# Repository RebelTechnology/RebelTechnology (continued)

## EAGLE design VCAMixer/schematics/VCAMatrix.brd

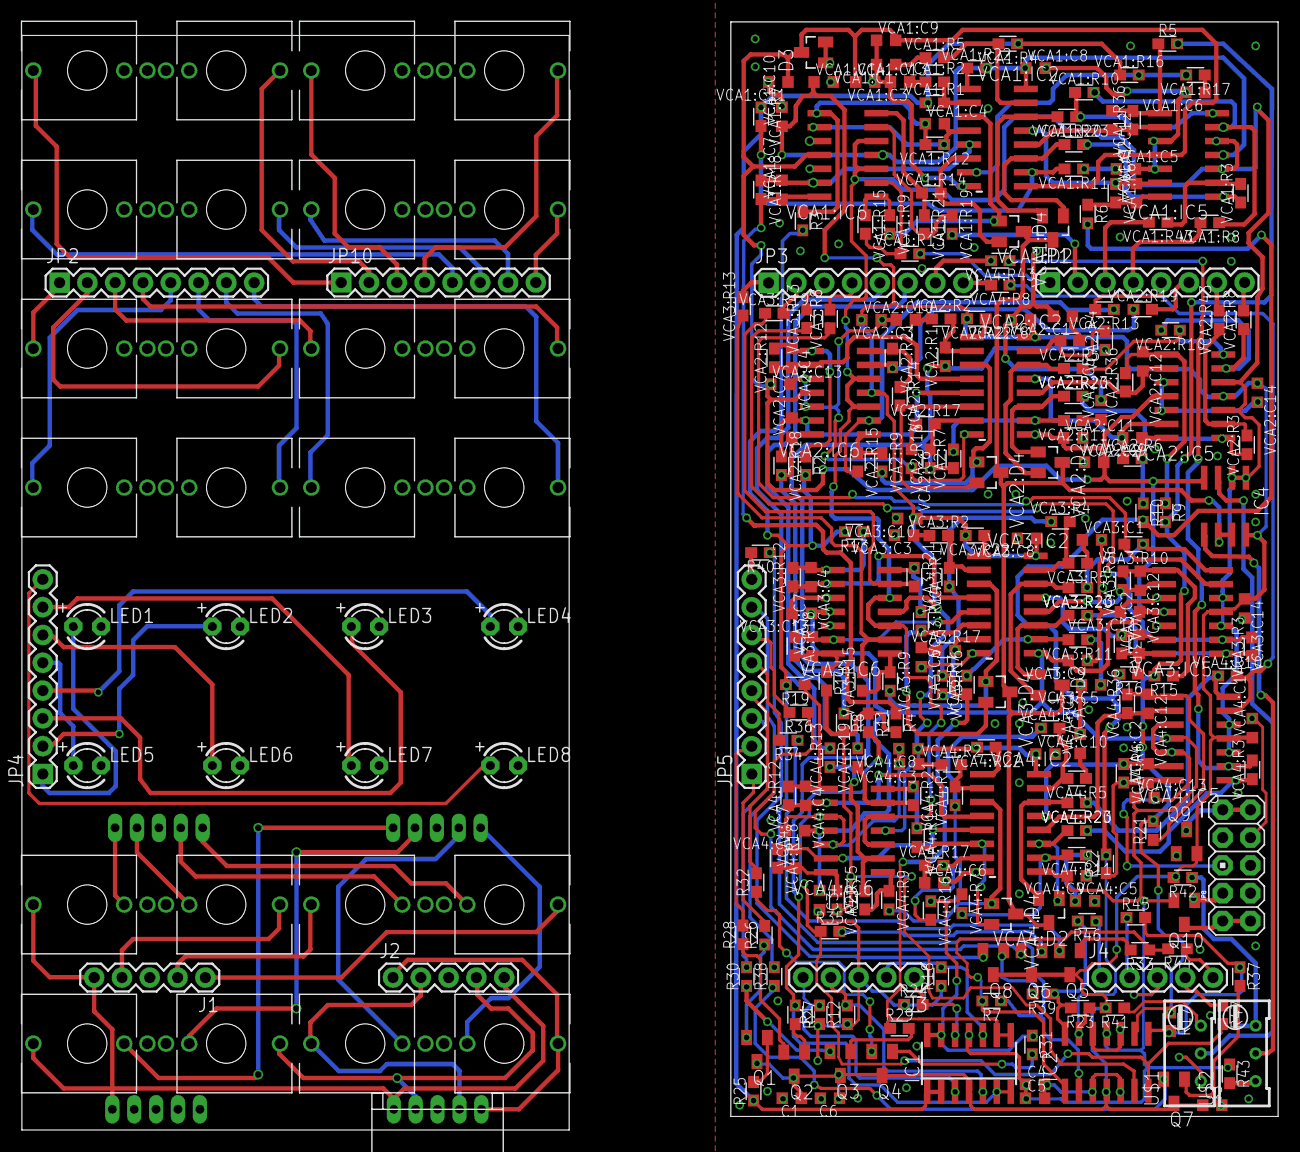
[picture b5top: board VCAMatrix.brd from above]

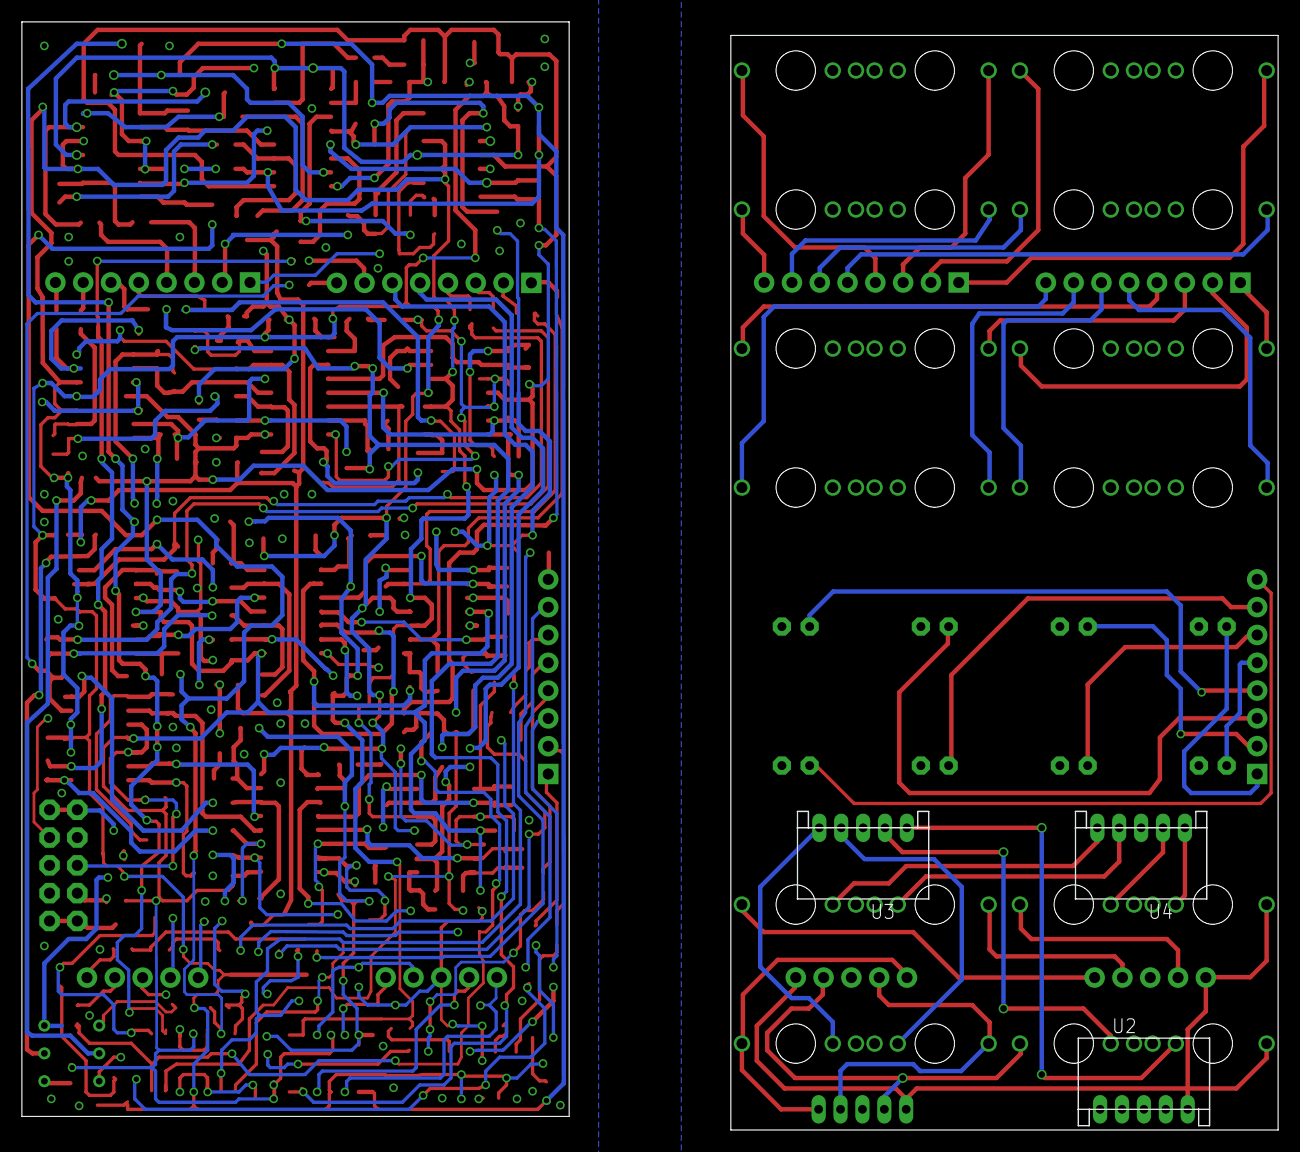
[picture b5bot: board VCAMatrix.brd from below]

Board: 2 copper layers, 50.0 x 100.0 mm, 292 parts (3 on the bottom side), 196 nets.

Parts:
C1, C2, C3, C4, C5, C6: 100n; C0603K
CV_AA: THONKICONN
CV_AB: THONKICONN
CV_AC: THONKICONN
CV_AD: THONKICONN
CV_BA: THONKICONN
CV_BB: THONKICONN
CV_BC: THONKICONN
CV_BD: THONKICONN
CV_CA: THONKICONN
CV_CB: THONKICONN
CV_CC: THONKICONN
CV_CD: THONKICONN
CV_DA: THONKICONN
CV_DB: THONKICONN
CV_DC: THONKICONN
CV_DD: THONKICONN
D3: BAT54A; SOT23
IC1: QUAD_OPAMPD; SO14
IC2: TL074D; SO14
IC4: TL072D; SO08
IN_A: THONKICONN
IN_B: THONKICONN
IN_C: THONKICONN
IN_D: THONKICONN
J1, J2, J3, J4: 1X05
JP1, JP2, JP3, JP4, JP5, JP10: 1X08
JP8: M05X2PTH; AVR_ICSP
LED1, LED2, LED3, LED4, LED5, LED6, LED7, LED8: LED3MM
OUTA: THONKICONN
OUTB: THONKICONN
OUTC: THONKICONN
OUTD: THONKICONN
Q1, Q2, Q3, Q4, Q5, Q6, Q7, Q8: BC846ALT1SMD; SOT23
Q9: BSS84; SOT23
Q10: BSS123; SOT23
R1, R2, R3, R4, R5, R6, R7, R8, R9, R10, R11, R12, R13, R14, R15, R16, R17, R18, R19, R20, R21, R22, R23, R24: 100k; 0603
R25, R27, R29, R31, R33, R35, R37, R39: 20k; 0603
R26, R28, R30, R32, R34, R36, R38, R40: 560; 0603
R41, R42, R43: 10k; 0603
R44, R45, R46, R47: 1k; 0603
U1, U2, U3, U4: CON-JST_PH_5W
U$1, U$2: RTRIM64W
VCA1:C1, VCA1:C3, VCA1:C5, VCA1:C6, VCA2:C1, VCA2:C3, VCA2:C5, VCA2:C6, VCA3:C1, VCA3:C3, VCA3:C5, VCA3:C6, VCA4:C1, VCA4:C3, VCA4:C5, VCA4:C6: 560p; C0603K
VCA1:C2, VCA1:C4, VCA1:C7, VCA1:C12, VCA2:C2, VCA2:C4, VCA2:C7, VCA2:C12, VCA3:C2, VCA3:C4, VCA3:C7, VCA3:C12, VCA4:C2, VCA4:C4, VCA4:C7, VCA4:C12: 100p; C0603K
VCA1:C8, VCA1:C9, VCA1:C10, VCA1:C11, VCA1:C13, VCA1:C14, VCA2:C8, VCA2:C9, VCA2:C10, VCA2:C11, VCA2:C13, VCA2:C14, VCA3:C8, VCA3:C9, VCA3:C10, VCA3:C11, VCA3:C13, VCA3:C14, VCA4:C8, VCA4:C9, VCA4:C10, VCA4:C11, VCA4:C13, VCA4:C14: 100n; C0603K
VCA1:D2, VCA1:D4, VCA2:D2, VCA2:D4, VCA3:D2, VCA3:D4, VCA4:D2, VCA4:D4: BAT54A; SOT23
VCA1:IC2, VCA2:IC2, VCA3:IC2, VCA4:IC2: SSM2164S; SOIC16N
VCA1:IC5, VCA1:IC6, VCA2:IC5, VCA2:IC6, VCA3:IC5, VCA3:IC6, VCA4:IC5, VCA4:IC6: TL074D; SO14
VCA1:R1, VCA1:R4, VCA1:R6, VCA1:R7, VCA1:R12, VCA1:R16, VCA1:R18, VCA1:R36, VCA2:R1, VCA2:R4, VCA2:R6, VCA2:R7, VCA2:R12, VCA2:R16, VCA2:R18, VCA2:R36, VCA3:R1, VCA3:R4, VCA3:R6, VCA3:R7, VCA3:R12, VCA3:R16, VCA3:R18, VCA3:R36, VCA4:R1, VCA4:R4, VCA4:R6, VCA4:R7, VCA4:R12, VCA4:R16, VCA4:R18, VCA4:R36: 30k; 0603
VCA1:R2, VCA1:R5, VCA1:R11, VCA1:R17, VCA2:R2, VCA2:R5, VCA2:R11, VCA2:R17, VCA3:R2, VCA3:R5, VCA3:R11, VCA3:R17, VCA4:R2, VCA4:R5, VCA4:R11, VCA4:R17: 500; 0603
VCA1:R3, VCA1:R10, VCA1:R15, VCA1:R21, VCA2:R3, VCA2:R10, VCA2:R15, VCA2:R21, VCA3:R3, VCA3:R10, VCA3:R15, VCA3:R21, VCA4:R3, VCA4:R10, VCA4:R15, VCA4:R21: 68k; 0603
VCA1:R8, VCA1:R13, VCA1:R19, VCA1:R43, VCA2:R8, VCA2:R13, VCA2:R19, VCA2:R43, VCA3:R8, VCA3:R13, VCA3:R19, VCA3:R43, VCA4:R8, VCA4:R13, VCA4:R19, VCA4:R43: 100k; 0603
VCA1:R9, VCA1:R14, VCA1:R20, VCA1:R23, VCA2:R9, VCA2:R14, VCA2:R20, VCA2:R23, VCA3:R9, VCA3:R14, VCA3:R20, VCA3:R23, VCA4:R9, VCA4:R14, VCA4:R20, VCA4:R23: 560; 0603
VCA1:R22, VCA2:R22, VCA3:R22, VCA4:R22: 6k; 0603

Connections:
+12V: C1.1, C2.1, C6.1, IC1.4, IC2.4, IC4.8, Q1.3, Q2.3, Q3.3, Q4.3, Q5.3, Q6.3, Q7.3, Q8.3, Q9.2, R41.2, R42.2, VCA1:C8.1, VCA1:C10.1, VCA1:C14.1, VCA1:IC2.16, VCA1:IC5.4, VCA1:IC6.4, VCA1:R22.2, VCA2:C8.1, VCA2:C10.1, VCA2:C14.1, VCA2:IC2.16, VCA2:IC5.4, VCA2:IC6.4, VCA2:R22.2, VCA3:C8.1, VCA3:C10.1, VCA3:C14.1, VCA3:IC2.16, VCA3:IC5.4, VCA3:IC6.4, VCA3:R22.2, VCA4:C8.1, VCA4:C10.1, VCA4:C14.1, VCA4:IC2.16, VCA4:IC5.4, VCA4:IC6.4, VCA4:R22.2
-12V: C3.1, C4.1, C5.1, D3.3, IC1.11, IC2.11, IC4.4, Q10.2, R43.1, VCA1:C9.2, VCA1:C11.1, VCA1:C13.1, VCA1:IC2.9, VCA1:IC5.11, VCA1:IC6.11, VCA2:C9.2, VCA2:C11.1, VCA2:C13.1, VCA2:IC2.9, VCA2:IC5.11, VCA2:IC6.11, VCA3:C9.2, VCA3:C11.1, VCA3:C13.1, VCA3:IC2.9, VCA3:IC5.11, VCA3:IC6.11, VCA4:C9.2, VCA4:C11.1, VCA4:C13.1, VCA4:IC2.9, VCA4:IC5.11, VCA4:IC6.11
CLAMP_REF: IC4.6, IC4.7, VCA1:D2.3, VCA1:D4.3, VCA2:D2.3, VCA2:D4.3, VCA3:D2.3, VCA3:D4.3, VCA4:D2.3, VCA4:D4.3
CV_AA: CV_AA.P$3, JP1.1, JP10.1, VCA1:R13.2
CV_AB: CV_AB.P$3, JP1.2, JP10.2, VCA1:R19.2
CV_AC: CV_AC.P$3, JP1.3, JP10.3, VCA1:R43.2
CV_AD: CV_AD.P$3, JP1.4, JP10.4, VCA1:R8.2
CV_BA: CV_BA.P$3, JP1.5, JP10.5, VCA2:R13.2
CV_BB: CV_BB.P$3, JP1.6, JP10.6, VCA2:R19.2
CV_BC: CV_BC.P$3, JP1.7, JP10.7, VCA2:R43.2
CV_BD: CV_BD.P$3, JP1.8, JP10.8, VCA2:R8.2
CV_CA: CV_CA.P$3, JP2.1, JP3.1, VCA3:R13.2
CV_CB: CV_CB.P$3, JP2.2, JP3.2, VCA3:R19.2
CV_CC: CV_CC.P$3, JP2.3, JP3.3, VCA3:R43.2
CV_CD: CV_CD.P$3, JP2.4, JP3.4, VCA3:R8.2
CV_DA: CV_DA.P$3, JP2.5, JP3.5, VCA4:R13.2
CV_DB: CV_DB.P$3, JP2.6, JP3.6, VCA4:R19.2
CV_DC: CV_DC.P$3, JP2.7, JP3.7, VCA4:R43.2
CV_DD: CV_DD.P$3, JP2.8, JP3.8, VCA4:R8.2
GND: C1.2, C2.2, C3.2, C4.2, C5.2, C6.2, CV_AA.P$1, CV_AA.P$2, CV_AB.P$1, CV_AB.P$2, CV_AC.P$1, CV_AC.P$2, CV_AD.P$1, CV_AD.P$2, CV_BA.P$1, CV_BA.P$2, CV_BB.P$1, CV_BB.P$2, CV_BC.P$1, CV_BC.P$2, CV_BD.P$1, CV_BD.P$2, CV_CA.P$1, CV_CA.P$2, CV_CB.P$1, CV_CB.P$2, CV_CC.P$1, CV_CC.P$2, CV_CD.P$1, CV_CD.P$2, CV_DA.P$1, CV_DA.P$2, CV_DB.P$1, CV_DB.P$2, CV_DC.P$1, CV_DC.P$2, CV_DD.P$1, CV_DD.P$2, D3.1, D3.2, IC2.3, IC2.5, IC2.10, IC2.12, IN_A.P$1, IN_B.P$1, IN_C.P$1, IN_D.P$1, J1.3, J2.3, J3.3, J4.3, JP8.3, JP8.4, JP8.5, JP8.6, JP8.7, JP8.8, LED1.K, LED2.K, LED3.K, LED4.K, LED5.K, LED6.K, LED7.K, LED8.K, OUTA.P$1, OUTB.P$1, OUTC.P$1, OUTD.P$1, Q9.1, Q10.1, R1.1, R12.1, R18.1, R24.1, U1.P3, U2.P3, U3.P3, U4.P3, U$1.1, VCA1:C1.2, VCA1:C3.2, VCA1:C5.2, VCA1:C6.2, VCA1:C8.2, VCA1:C9.1, VCA1:C10.2, VCA1:C11.2, VCA1:C13.2, VCA1:C14.2, VCA1:IC2.8, VCA1:IC5.10, VCA1:IC5.12, VCA1:IC6.10, VCA1:IC6.12, VCA2:C1.2, VCA2:C3.2, VCA2:C5.2, VCA2:C6.2, VCA2:C8.2, VCA2:C9.1, VCA2:C10.2, VCA2:C11.2, VCA2:C13.2, VCA2:C14.2, VCA2:IC2.8, VCA2:IC5.10, VCA2:IC5.12, VCA2:IC6.10, VCA2:IC6.12, VCA3:C1.2, VCA3:C3.2, VCA3:C5.2, VCA3:C6.2, VCA3:C8.2, VCA3:C9.1, VCA3:C10.2, VCA3:C11.2, VCA3:C13.2, VCA3:C14.2, VCA3:IC2.8, VCA3:IC5.10, VCA3:IC5.12, VCA3:IC6.10, VCA3:IC6.12, VCA4:C1.2, VCA4:C3.2, VCA4:C5.2, VCA4:C6.2, VCA4:C8.2, VCA4:C9.1, VCA4:C10.2, VCA4:C11.2, VCA4:C13.2, VCA4:C14.2, VCA4:IC2.8, VCA4:IC5.10, VCA4:IC5.12, VCA4:IC6.10, VCA4:IC6.12
IN_A: IC1.3, IN_A.P$3, J1.5, J3.5, R1.2, U2.P1
IN_B: IC1.5, IN_B.P$3, J1.4, J3.4, R12.2, U2.P2
IN_C: IC1.10, IN_C.P$3, J1.2, J3.2, R18.2, U2.P4
IN_D: IC1.12, IN_D.P$3, J1.1, J3.1, R24.2, U2.P5
LED_1: JP4.1, JP5.1, LED1.A, R26.2
LED_2: JP4.2, JP5.2, LED2.A, R28.2
LED_3: JP4.3, JP5.3, LED3.A, R30.2
LED_4: JP4.4, JP5.4, LED4.A, R32.2
LED_5: JP4.5, JP5.5, LED5.A, R34.2
LED_6: JP4.6, JP5.6, LED6.A, R36.2
LED_7: JP4.7, JP5.7, LED7.A, R38.2
LED_8: JP4.8, JP5.8, LED8.A, R40.2
unnamed: IC1.6, IC1.7, R27.1, VCA2:R1.1, VCA2:R4.1, VCA2:R7.1, VCA2:R16.1
unnamed: Q1.2, R26.1
unnamed: JP8.9, JP8.10, Q10.3
unnamed: R3.1, VCA1:C4.1, VCA1:IC6.8, VCA1:R12.2
unnamed: R4.1, VCA1:C7.1, VCA1:IC6.14, VCA1:R18.2
unnamed: R5.1, VCA1:C12.1, VCA1:IC5.8, VCA1:R36.2
unnamed: R6.1, VCA1:C2.1, VCA1:IC5.14, VCA1:R6.2
unnamed: IC2.9, R5.2, R9.2, R15.2, R17.1, R21.2
unnamed: R41.1, U$1.3
unnamed: R2.1, VCA2:C4.1, VCA2:IC6.8, VCA2:R12.2
unnamed: R8.1, VCA2:C7.1, VCA2:IC6.14, VCA2:R18.2
unnamed: R9.1, VCA2:C12.1, VCA2:IC5.8, VCA2:R36.2
unnamed: R10.1, VCA2:C2.1, VCA2:IC5.14, VCA2:R6.2
unnamed: Q1.1, R25.2
unnamed: IC1.13, IC1.14, R31.1, VCA4:R1.1, VCA4:R4.1, VCA4:R7.1, VCA4:R16.1
unnamed: IC1.8, IC1.9, R29.1, VCA3:R1.1, VCA3:R4.1, VCA3:R7.1, VCA3:R16.1
unnamed: Q8.2, R40.1
unnamed: R13.1, VCA3:C4.1, VCA3:IC6.8, VCA3:R12.2
unnamed: R14.1, VCA3:C7.1, VCA3:IC6.14, VCA3:R18.2
unnamed: R15.1, VCA3:C12.1, VCA3:IC5.8, VCA3:R36.2
unnamed: R16.1, VCA3:C2.1, VCA3:IC5.14, VCA3:R6.2
unnamed: IC4.3, U$1.2
unnamed: IC4.1, IC4.2, VCA1:IC5.3, VCA1:IC5.5, VCA1:IC6.3, VCA1:IC6.5, VCA2:IC5.3, VCA2:IC5.5, VCA2:IC6.3, VCA2:IC6.5, VCA3:IC5.3, VCA3:IC5.5, VCA3:IC6.3, VCA3:IC6.5, VCA4:IC5.3, VCA4:IC5.5, VCA4:IC6.3, VCA4:IC6.5
unnamed: R19.1, VCA4:C4.1, VCA4:IC6.8, VCA4:R12.2
unnamed: R20.1, VCA4:C7.1, VCA4:IC6.14, VCA4:R18.2
unnamed: R21.1, VCA4:C12.1, VCA4:IC5.8, VCA4:R36.2
unnamed: R22.1, VCA4:C2.1, VCA4:IC5.14, VCA4:R6.2
unnamed: R42.1, U$2.3
unnamed: Q6.1, R35.2
unnamed: Q2.1, R27.2
unnamed: IC2.13, R6.2, R10.2, R16.2, R22.2, R23.1
unnamed: Q2.2, R28.1
unnamed: Q3.1, R29.2
unnamed: Q3.2, R30.1
unnamed: Q6.2, R36.1
unnamed: OUTA.P$2, U3.P5
unnamed: Q4.1, R31.2
unnamed: IC2.2, R2.2, R3.2, R7.1, R13.2, R19.2
unnamed: IC2.6, R4.2, R8.2, R11.1, R14.2, R20.2
unnamed: Q4.2, R32.1
unnamed: Q7.1, R37.2
unnamed: Q5.1, R33.2
unnamed: Q5.2, R34.1
unnamed: Q7.2, R38.1
unnamed: Q8.1, R39.2
unnamed: IN_B.P$2, U4.P4
unnamed: IN_C.P$2, U4.P2
unnamed: IN_D.P$2, U4.P1
unnamed: OUTB.P$2, U3.P4
unnamed: OUTC.P$2, U3.P2
unnamed: OUTD.P$2, U3.P1
unnamed: IN_A.P$2, U4.P5
unnamed: R43.2, U$2.1
unnamed: IC4.5, U$2.2
unnamed: JP8.1, JP8.2, Q9.3
unnamed: IC1.1, IC1.2, R25.1, VCA1:R1.1, VCA1:R4.1, VCA1:R7.1, VCA1:R16.1
OUTPUT_A: IC2.1, R7.2, R33.1, R44.2
OUTPUT_B: IC2.7, R11.2, R35.1, R47.2
OUTPUT_C: IC2.8, R17.2, R37.1, R45.2
OUTPUT_D: IC2.14, R23.2, R39.1, R46.2
OUT_A: J2.5, J4.5, OUTA.P$3, R44.1, U1.P1
OUT_B: J2.4, J4.4, OUTB.P$3, R47.1, U1.P2
OUT_C: J2.2, J4.2, OUTC.P$3, R45.1, U1.P4
OUT_D: J2.1, J4.1, OUTD.P$3, R46.1, U1.P5
VCA1:IC2_1: VCA1:IC5.7, VCA1:R10.1, VCA1:R20.1
VCA1:IC2_2: VCA1:IC5.6, VCA1:R8.1, VCA1:R10.2
VCA1:IC2_3: VCA1:IC6.1, VCA1:R9.1, VCA1:R15.1
VCA1:IC2_4: VCA1:IC5.2, VCA1:R3.2, VCA1:R43.1
VCA1:IC2_5: VCA1:IC6.2, VCA1:R13.1, VCA1:R15.2
VCA1:IC2_6: VCA1:IC6.7, VCA1:R14.1, VCA1:R21.1
VCA1:IC2_7: VCA1:IC6.6, VCA1:R19.1, VCA1:R21.2
VCA1:IC2_11: VCA1:IC5.1, VCA1:R3.1, VCA1:R23.2
VCA1:N$1: VCA1:D4.1, VCA1:IC2.3, VCA1:R9.2
VCA1:N$2: VCA1:C1.1, VCA1:R5.1
VCA1:N$3: VCA1:C3.1, VCA1:R2.1
VCA1:N$4: VCA1:IC2.15, VCA1:R4.2, VCA1:R5.2
VCA1:N$5: VCA1:IC2.2, VCA1:R1.2, VCA1:R2.2
VCA1:N$6: VCA1:C2.2, VCA1:IC2.13, VCA1:IC5.13, VCA1:R6.1
VCA1:N$7: VCA1:D4.2, VCA1:IC2.6, VCA1:R14.2
VCA1:N$8: VCA1:D2.1, VCA1:IC2.11, VCA1:R23.1
VCA1:N$9: VCA1:C4.2, VCA1:IC2.4, VCA1:IC6.9, VCA1:R12.1
VCA1:N$11: VCA1:C6.1, VCA1:R17.1
VCA1:N$12: VCA1:IC2.7, VCA1:R16.2, VCA1:R17.2
VCA1:N$13: VCA1:C7.2, VCA1:IC2.5, VCA1:IC6.13, VCA1:R18.1
VCA1:N$14: VCA1:D2.2, VCA1:IC2.14, VCA1:R20.2
VCA1:N$17: VCA1:IC2.1, VCA1:R22.1
VCA1:N$19: VCA1:C5.1, VCA1:R11.1
VCA1:N$23: VCA1:IC2.10, VCA1:R7.2, VCA1:R11.2
VCA1:N$49: VCA1:C12.2, VCA1:IC2.12, VCA1:IC5.9, VCA1:R36.1
VCA2:IC2_1: VCA2:IC5.7, VCA2:R10.1, VCA2:R20.1
VCA2:IC2_2: VCA2:IC5.6, VCA2:R8.1, VCA2:R10.2
VCA2:IC2_3: VCA2:IC6.1, VCA2:R9.1, VCA2:R15.1
VCA2:IC2_4: VCA2:IC5.2, VCA2:R3.2, VCA2:R43.1
VCA2:IC2_5: VCA2:IC6.2, VCA2:R13.1, VCA2:R15.2
VCA2:IC2_6: VCA2:IC6.7, VCA2:R14.1, VCA2:R21.1
VCA2:IC2_7: VCA2:IC6.6, VCA2:R19.1, VCA2:R21.2
VCA2:IC2_11: VCA2:IC5.1, VCA2:R3.1, VCA2:R23.2
VCA2:N$1: VCA2:D4.1, VCA2:IC2.3, VCA2:R9.2
VCA2:N$2: VCA2:C1.1, VCA2:R5.1
VCA2:N$3: VCA2:C3.1, VCA2:R2.1
VCA2:N$4: VCA2:IC2.15, VCA2:R4.2, VCA2:R5.2
VCA2:N$5: VCA2:IC2.2, VCA2:R1.2, VCA2:R2.2
VCA2:N$6: VCA2:C2.2, VCA2:IC2.13, VCA2:IC5.13, VCA2:R6.1
VCA2:N$7: VCA2:D4.2, VCA2:IC2.6, VCA2:R14.2
VCA2:N$8: VCA2:D2.1, VCA2:IC2.11, VCA2:R23.1
VCA2:N$9: VCA2:C4.2, VCA2:IC2.4, VCA2:IC6.9, VCA2:R12.1
VCA2:N$11: VCA2:C6.1, VCA2:R17.1
VCA2:N$12: VCA2:IC2.7, VCA2:R16.2, VCA2:R17.2
VCA2:N$13: VCA2:C7.2, VCA2:IC2.5, VCA2:IC6.13, VCA2:R18.1
VCA2:N$14: VCA2:D2.2, VCA2:IC2.14, VCA2:R20.2
VCA2:N$17: VCA2:IC2.1, VCA2:R22.1
VCA2:N$19: VCA2:C5.1, VCA2:R11.1
VCA2:N$23: VCA2:IC2.10, VCA2:R7.2, VCA2:R11.2
VCA2:N$49: VCA2:C12.2, VCA2:IC2.12, VCA2:IC5.9, VCA2:R36.1
VCA3:IC2_1: VCA3:IC5.7, VCA3:R10.1, VCA3:R20.1
VCA3:IC2_2: VCA3:IC5.6, VCA3:R8.1, VCA3:R10.2
VCA3:IC2_3: VCA3:IC6.1, VCA3:R9.1, VCA3:R15.1
VCA3:IC2_4: VCA3:IC5.2, VCA3:R3.2, VCA3:R43.1
VCA3:IC2_5: VCA3:IC6.2, VCA3:R13.1, VCA3:R15.2
VCA3:IC2_6: VCA3:IC6.7, VCA3:R14.1, VCA3:R21.1
VCA3:IC2_7: VCA3:IC6.6, VCA3:R19.1, VCA3:R21.2
VCA3:IC2_11: VCA3:IC5.1, VCA3:R3.1, VCA3:R23.2
VCA3:N$1: VCA3:D4.1, VCA3:IC2.3, VCA3:R9.2
VCA3:N$2: VCA3:C1.1, VCA3:R5.1
VCA3:N$3: VCA3:C3.1, VCA3:R2.1
VCA3:N$4: VCA3:IC2.15, VCA3:R4.2, VCA3:R5.2
VCA3:N$5: VCA3:IC2.2, VCA3:R1.2, VCA3:R2.2
VCA3:N$6: VCA3:C2.2, VCA3:IC2.13, VCA3:IC5.13, VCA3:R6.1
VCA3:N$7: VCA3:D4.2, VCA3:IC2.6, VCA3:R14.2
VCA3:N$8: VCA3:D2.1, VCA3:IC2.11, VCA3:R23.1
VCA3:N$9: VCA3:C4.2, VCA3:IC2.4, VCA3:IC6.9, VCA3:R12.1
VCA3:N$11: VCA3:C6.1, VCA3:R17.1
VCA3:N$12: VCA3:IC2.7, VCA3:R16.2, VCA3:R17.2
VCA3:N$13: VCA3:C7.2, VCA3:IC2.5, VCA3:IC6.13, VCA3:R18.1
VCA3:N$14: VCA3:D2.2, VCA3:IC2.14, VCA3:R20.2
VCA3:N$17: VCA3:IC2.1, VCA3:R22.1
VCA3:N$19: VCA3:C5.1, VCA3:R11.1
VCA3:N$23: VCA3:IC2.10, VCA3:R7.2, VCA3:R11.2
VCA3:N$49: VCA3:C12.2, VCA3:IC2.12, VCA3:IC5.9, VCA3:R36.1
VCA4:IC2_1: VCA4:IC5.7, VCA4:R10.1, VCA4:R20.1
VCA4:IC2_2: VCA4:IC5.6, VCA4:R8.1, VCA4:R10.2
VCA4:IC2_3: VCA4:IC6.1, VCA4:R9.1, VCA4:R15.1
VCA4:IC2_4: VCA4:IC5.2, VCA4:R3.2, VCA4:R43.1
VCA4:IC2_5: VCA4:IC6.2, VCA4:R13.1, VCA4:R15.2
VCA4:IC2_6: VCA4:IC6.7, VCA4:R14.1, VCA4:R21.1
VCA4:IC2_7: VCA4:IC6.6, VCA4:R19.1, VCA4:R21.2
VCA4:IC2_11: VCA4:IC5.1, VCA4:R3.1, VCA4:R23.2
VCA4:N$1: VCA4:D4.1, VCA4:IC2.3, VCA4:R9.2
VCA4:N$2: VCA4:C1.1, VCA4:R5.1
VCA4:N$3: VCA4:C3.1, VCA4:R2.1
VCA4:N$4: VCA4:IC2.15, VCA4:R4.2, VCA4:R5.2
VCA4:N$5: VCA4:IC2.2, VCA4:R1.2, VCA4:R2.2
VCA4:N$6: VCA4:C2.2, VCA4:IC2.13, VCA4:IC5.13, VCA4:R6.1
VCA4:N$7: VCA4:D4.2, VCA4:IC2.6, VCA4:R14.2
VCA4:N$8: VCA4:D2.1, VCA4:IC2.11, VCA4:R23.1
VCA4:N$9: VCA4:C4.2, VCA4:IC2.4, VCA4:IC6.9, VCA4:R12.1
VCA4:N$11: VCA4:C6.1, VCA4:R17.1
VCA4:N$12: VCA4:IC2.7, VCA4:R16.2, VCA4:R17.2
VCA4:N$13: VCA4:C7.2, VCA4:IC2.5, VCA4:IC6.13, VCA4:R18.1
VCA4:N$14: VCA4:D2.2, VCA4:IC2.14, VCA4:R20.2
VCA4:N$17: VCA4:IC2.1, VCA4:R22.1
VCA4:N$19: VCA4:C5.1, VCA4:R11.1
VCA4:N$23: VCA4:IC2.10, VCA4:R7.2, VCA4:R11.2
VCA4:N$49: VCA4:C12.2, VCA4:IC2.12, VCA4:IC5.9, VCA4:R36.1
